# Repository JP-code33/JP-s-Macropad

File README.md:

# JP-s-Macropad

This is my first hardware project, yayyy, anyways I have made a simple 6 key macropad which I will be using it for CAD as love to do CAD and I have used its simple
shortcuts in this macropad. I have also added a rotary encoder and an OLED Screen. 

# Schematic & PCB

This was my first time making a schematic but it was fairly quick to make. It was because I saw tons of amazing examples on Stardance and took inspiration from many of them which made the process super simple. 

Working with PCB design. It was easy because the schematic was right. As I was routing it I showed me where each pin should connect. There was overlapping in between but I used Via to have utilized both sides like the top and bottom to have no overlapping in between. 

# CAD

CAD was fairly easy as I mentioned it is made for CAD so I had prior experience in making it so easy for me to make a box. I added some triangles to add some design and added my name on it as a design. 

# How to flash firmware

What I have found the easiest way is to use QMK Toolbox, what I will do is connect the macropad to the computer and then load up the toolbox and load the files in toolbox. Then I will just use the inbuilt flash button to flash it to my macropad

# Assembly

I don't have the necessary parts yet but I waiting for them. I will be soldering the diodes and will do the wiring to connect everything up. I will then put it in the case and use the screws to tighten everything up. 

# Why I made it

I was wanted to buy a steamdeck which as I found those fascinating because you can program them and you could use it as whatever key you want but didn't really get a chance to buy and saw an opportunity to make my own so I decided to make one for CAD shortcuts!

# Bill Of Materials (BOM)

6x Cherry MX Switches

6x Keycaps 

1x EC11 Rotary Encoder

1x Seeed XIAO RP20404

4x M3x16mm screws

6x Diodes

1 case (2 parts)

1 PCB (JLCPCB only gives 5 so will have to buy the 5 pack)

1 soldering iron

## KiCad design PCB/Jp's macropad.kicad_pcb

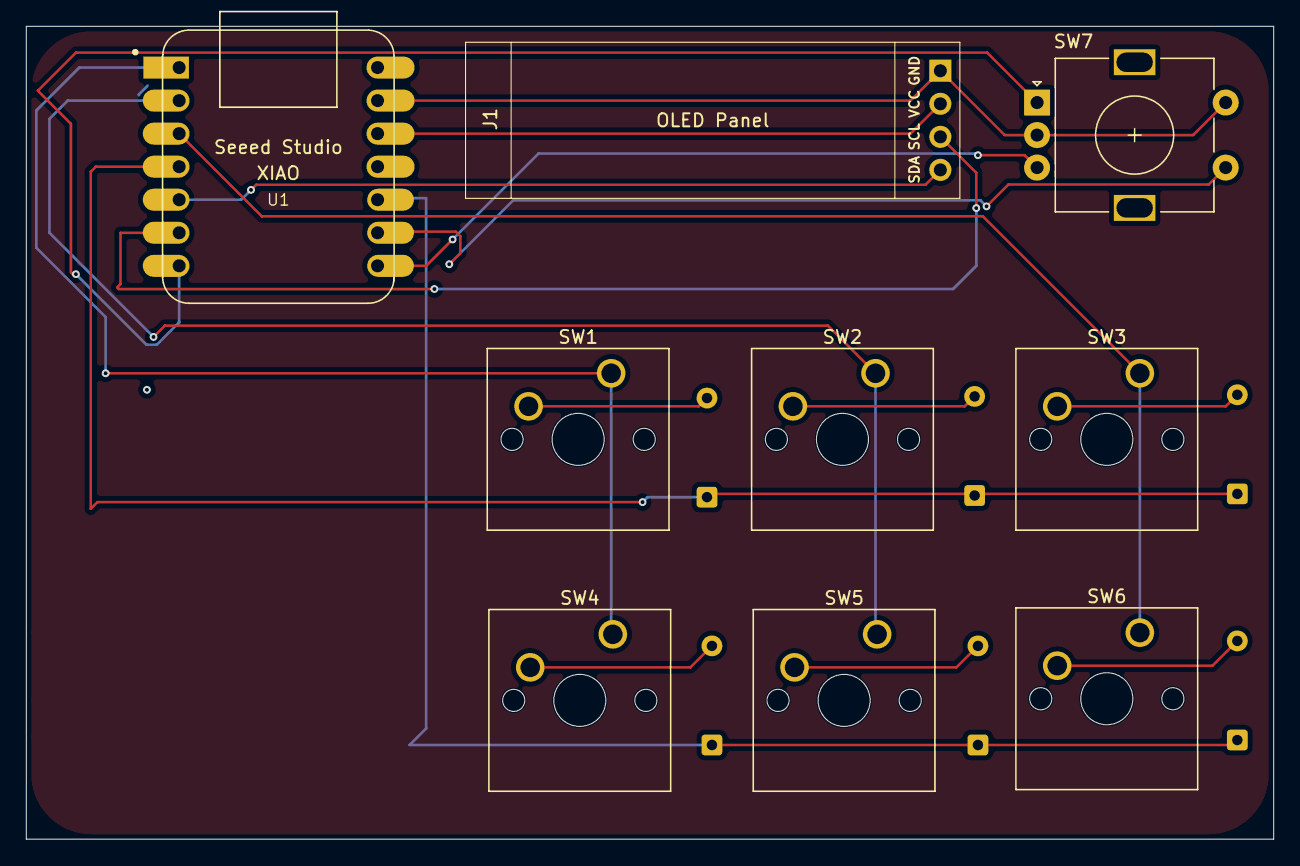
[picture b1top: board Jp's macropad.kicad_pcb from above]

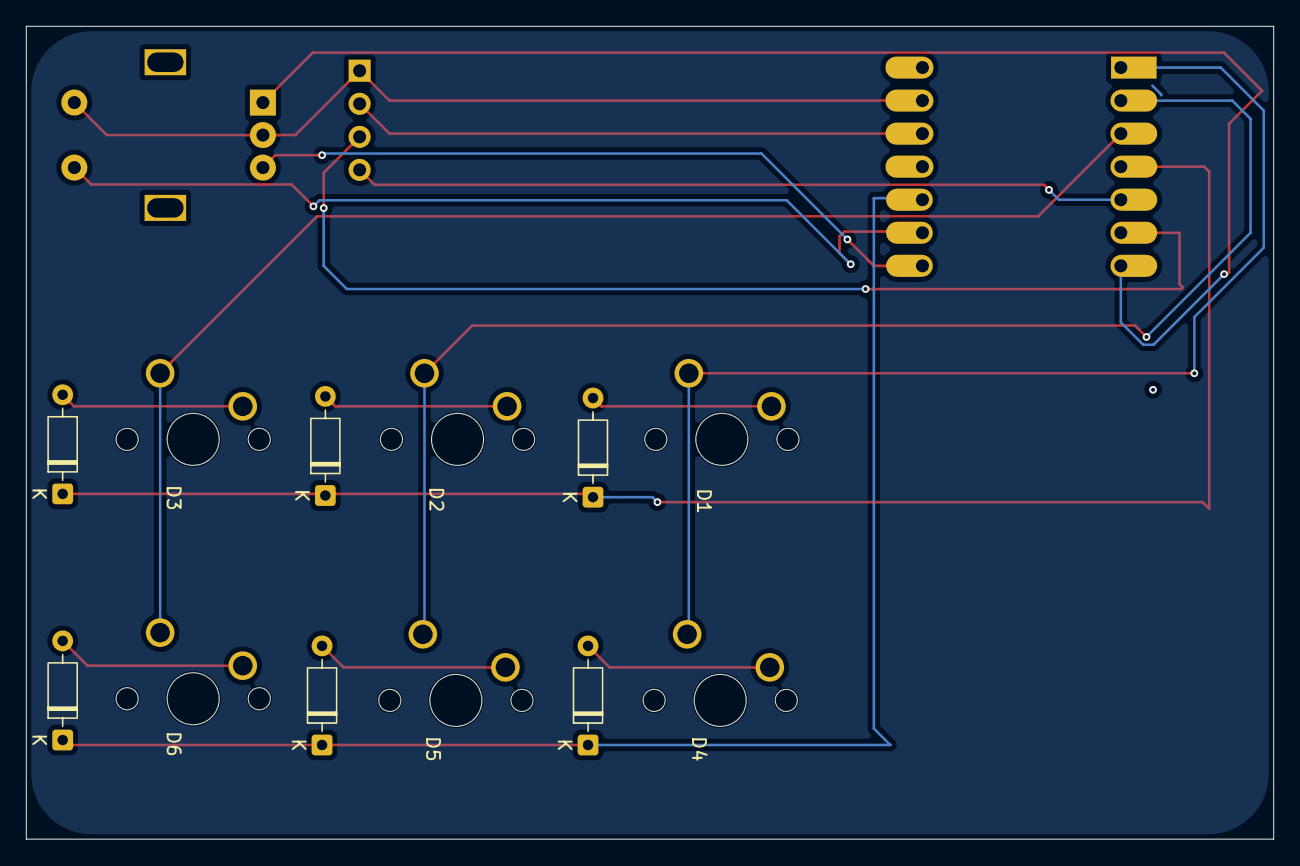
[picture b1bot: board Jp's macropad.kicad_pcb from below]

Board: 2 copper layers, 95.9 x 62.5 mm, 15 parts (6 on the bottom side), 18 nets.

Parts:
D1, D2, D3, D4, D5, D6: 1N4148; D_DO-35_SOD27_P7.62mm_Horizontal
J1: Conn_01x04; SSD1306-0.91-OLED-4pin-128x32
SW1, SW2, SW3, SW4, SW5, SW6: SW_Push; SW_Cherry_MX_1.00u_PCB
SW7: RotaryEncoder_Switch; RotaryEncoder_Alps_EC11E-Switch_Vertical_H20mm
U1: MOUDLE-SEEEDUINO-XIAO; XIAO-Generic-Hybrid-14P-2.54-21X17.8MM

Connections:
/A to 7: SW7.A, U1.7 (PB08_A6_D6_TX)
/B to 8: SW7.B, U1.8 (PB09_A7_D7_RX)
/S1 to 9: SW7.S1, U1.9 (PA7_A8_D8_SCK)
Column 0: SW1.1, SW4.1, U1.1 (PA02_A0_D0)
Column 1: SW2.1, SW5.1, U1.2 (PA4_A1_D1)
Column 2: SW3.1, SW6.1, U1.3 (PA10_A2_D2)
GND: J1.1, SW7.C, SW7.S2, U1.13 (GND)
unnamed: D1.2 (A), SW1.2
unnamed: D2.2 (A), SW2.2
unnamed: D3.2 (A), SW3.2
unnamed: D4.2 (A), SW4.2
unnamed: D5.2 (A), SW5.2
unnamed: D6.2 (A), SW6.2
unnamed: J1.2, U1.12 (3V3)
unnamed: J1.3, U1.6 (PA9_A5_D5_SCL)
unnamed: J1.4, U1.5 (PA8_A4_D4_SDA)
Row 0: D1.1 (K), D2.1 (K), D3.1 (K), U1.4 (PA11_A3_D3)
Row 1: D4.1 (K), D5.1 (K), D6.1 (K), U1.10 (PA5_A9_D9_MISO)

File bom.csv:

Designator,Footprint,Quantity,Value,LCSC Part #
"D1, D2, D3, D4, D5, D6",D_DO-35_SOD27_P7.62mm_Horizontal,6,1N4148,
J1,SSD1306-0.91-OLED-4pin-128x32,1,Conn_01x04,
"SW1, SW2, SW3, SW4, SW5, SW6",SW_Cherry_MX_1.00u_PCB,6,SW_Push,
SW7,RotaryEncoder_Alps_EC11E-Switch_Vertical_H20mm,1,RotaryEncoder_Switch,
U1,XIAO-Generic-Hybrid-14P-2.54-21X17.8MM,1,MOUDLE-SEEEDUINO-XIAO,
